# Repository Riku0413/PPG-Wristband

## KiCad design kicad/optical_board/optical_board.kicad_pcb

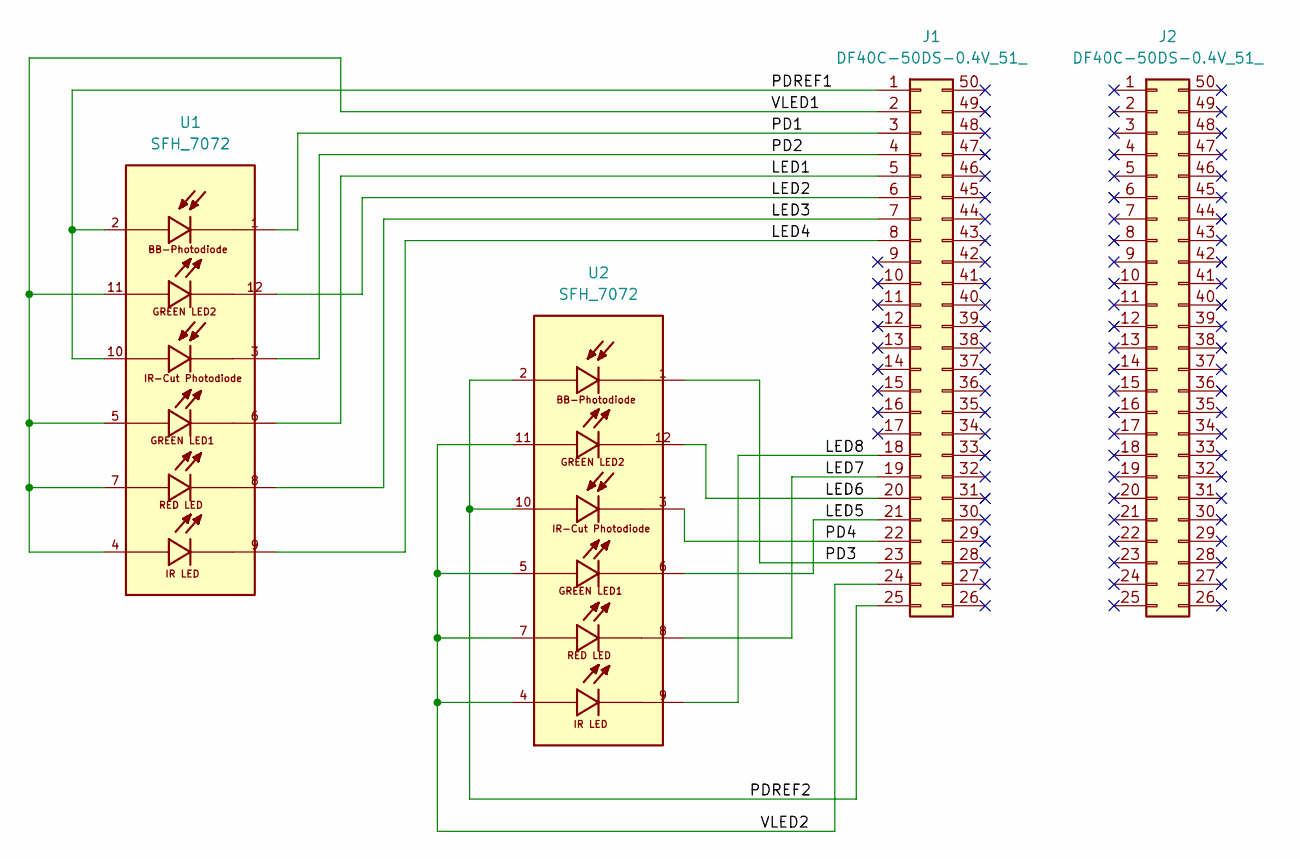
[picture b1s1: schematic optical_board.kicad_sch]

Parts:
J1, J2: DF40C-50DS-0.4V_51_
U1, U2: SFH_7072; SFH 7072; PARTREV 1.0

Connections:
/LED1: J1.5, U1.6
/LED2: J1.6, U1.12
/LED3: J1.7, U1.8
/LED4: J1.8, U1.9
/LED5: J1.21, U2.6
/LED6: J1.20, U2.12
/LED7: J1.19, U2.8
/LED8: J1.18, U2.9
/PD1: J1.3, U1.1
/PD2: J1.4, U1.3
/PD3: J1.23, U2.1
/PD4: J1.22, U2.3
/PDREF1: J1.1, U1.2, U1.10
/PDREF2: J1.25, U2.2, U2.10
/VLED1: J1.2, U1.4, U1.5, U1.7, U1.11
/VLED2: J1.24, U2.4, U2.5, U2.7, U2.11

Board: 2 copper layers, 4 parts (0 on the bottom side), 16 nets, no tracks yet.

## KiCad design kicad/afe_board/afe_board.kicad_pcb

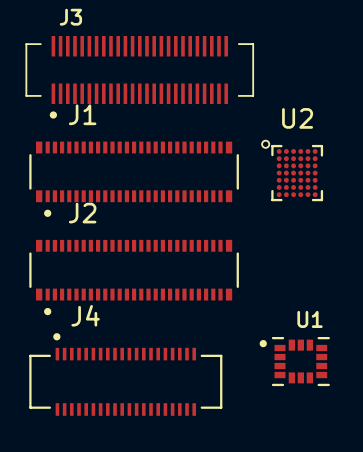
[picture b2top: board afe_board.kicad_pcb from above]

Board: 2 copper layers, 6 parts (0 on the bottom side), 22 nets, no tracks yet.

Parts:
J1, J2: DF40C-50DP-0.4V_51_
J3: DF40C-50DS-0.4V_51_
J4: DF40C-40DS-0.4V_51_
U1: LSM6DSOX
U2: AS7058; AS7058 WLCSP42

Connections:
/1V8: J3.6, J3.7, J3.41, U1.5 (VDDIO), U1.8 (VDD), U1.12 (CS), U2.E5 (IOVDD), U2.E6 (DVDD), U2.F1 (AVDD2), U2.G4 (AVDD1)
/4V5: J2.27, J2.49, J3.42, U2.C2 (VCSELS)
/I2C_A_SCL: J3.36, U1.13 (SCL)
/I2C_A_SDA: J3.35, U1.14 (SDA)
/LED1: J2.46, U2.A6 (LED1)
/LED2: J2.45, U2.B6 (LED2)
/LED3: J2.44, U2.A5 (LED3)
/LED4: J2.43, U2.A4 (LED4)
/LED5: J2.30, U2.A1 (LED5)
/LED6: J2.31, U2.B1 (LED6)
/LED7: J2.32, U2.A2 (LED7)
/LED8: J2.33, U2.A3 (LED8)
/PD1: J2.48, U2.E4 (PD1)
/PD2: J2.47, U2.G3 (PD2)
/PD3: J2.28, U2.F4 (PD3)
/PD4: J2.29, U2.D4
/PDREF: J2.26, J2.50, U2.G1 (PDREF)
/SPI_A_CS: J3.28, U2.B4 (CSXN)
/SPI_A_MISO: J3.34, U2.C4 (MISO)
/SPI_A_MOSI: J3.29, U2.C5 (SDA_MOSI)
/SPI_A_SCL: J3.31, U2.C6 (SCL)
GND: U1.2 (SDX), U1.3 (SCX), U1.6 (GND), U1.7 (GND), U2.B2 (PGND2), U2.B5 (PGND1), U2.D6 (DGND), U2.F2 (AGND2), U2.G5 (AGND1)

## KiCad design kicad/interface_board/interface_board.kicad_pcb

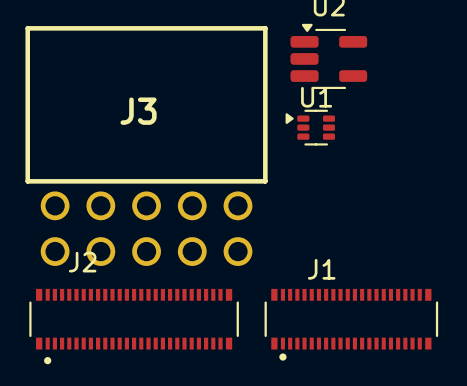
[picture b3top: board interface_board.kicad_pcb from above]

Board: 2 copper layers, 5 parts (0 on the bottom side), 10 nets, no tracks yet.

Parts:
J1: DF40C-40DP-0.4V_51_
J2: DF40C-50DP-0.4V_51_
J3: 613010243121; 613010243121 Angled Socket Header
U1: TPS61023; TPS61023DRLR_SOT-563
U2: TPS78218DDC; TPS78218DDCR_SOT-23-5

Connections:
/1V8: J2.6, J2.7, J2.41, U2.5 (OUT)
/3V: J3.6, J3.8, U1.2 (EN), U1.3 (VIN), U2.1 (IN), U2.3 (EN)
/4V5: J2.42, U1.6 (VOUT)
/I2C_A_SCL: J2.36, J3.2
/I2C_A_SDA: J2.35, J3.4
/SPI_A_CLK: J2.31, J3.3
/SPI_A_CS: J2.28, J3.7
/SPI_A_MISO: J2.34, J3.1
/SPI_A_MOSI: J2.29, J3.5
GND: U1.4 (GND), U2.2 (GND), U2.4 (GND)

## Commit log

2026-03-19 [add] initial commit
